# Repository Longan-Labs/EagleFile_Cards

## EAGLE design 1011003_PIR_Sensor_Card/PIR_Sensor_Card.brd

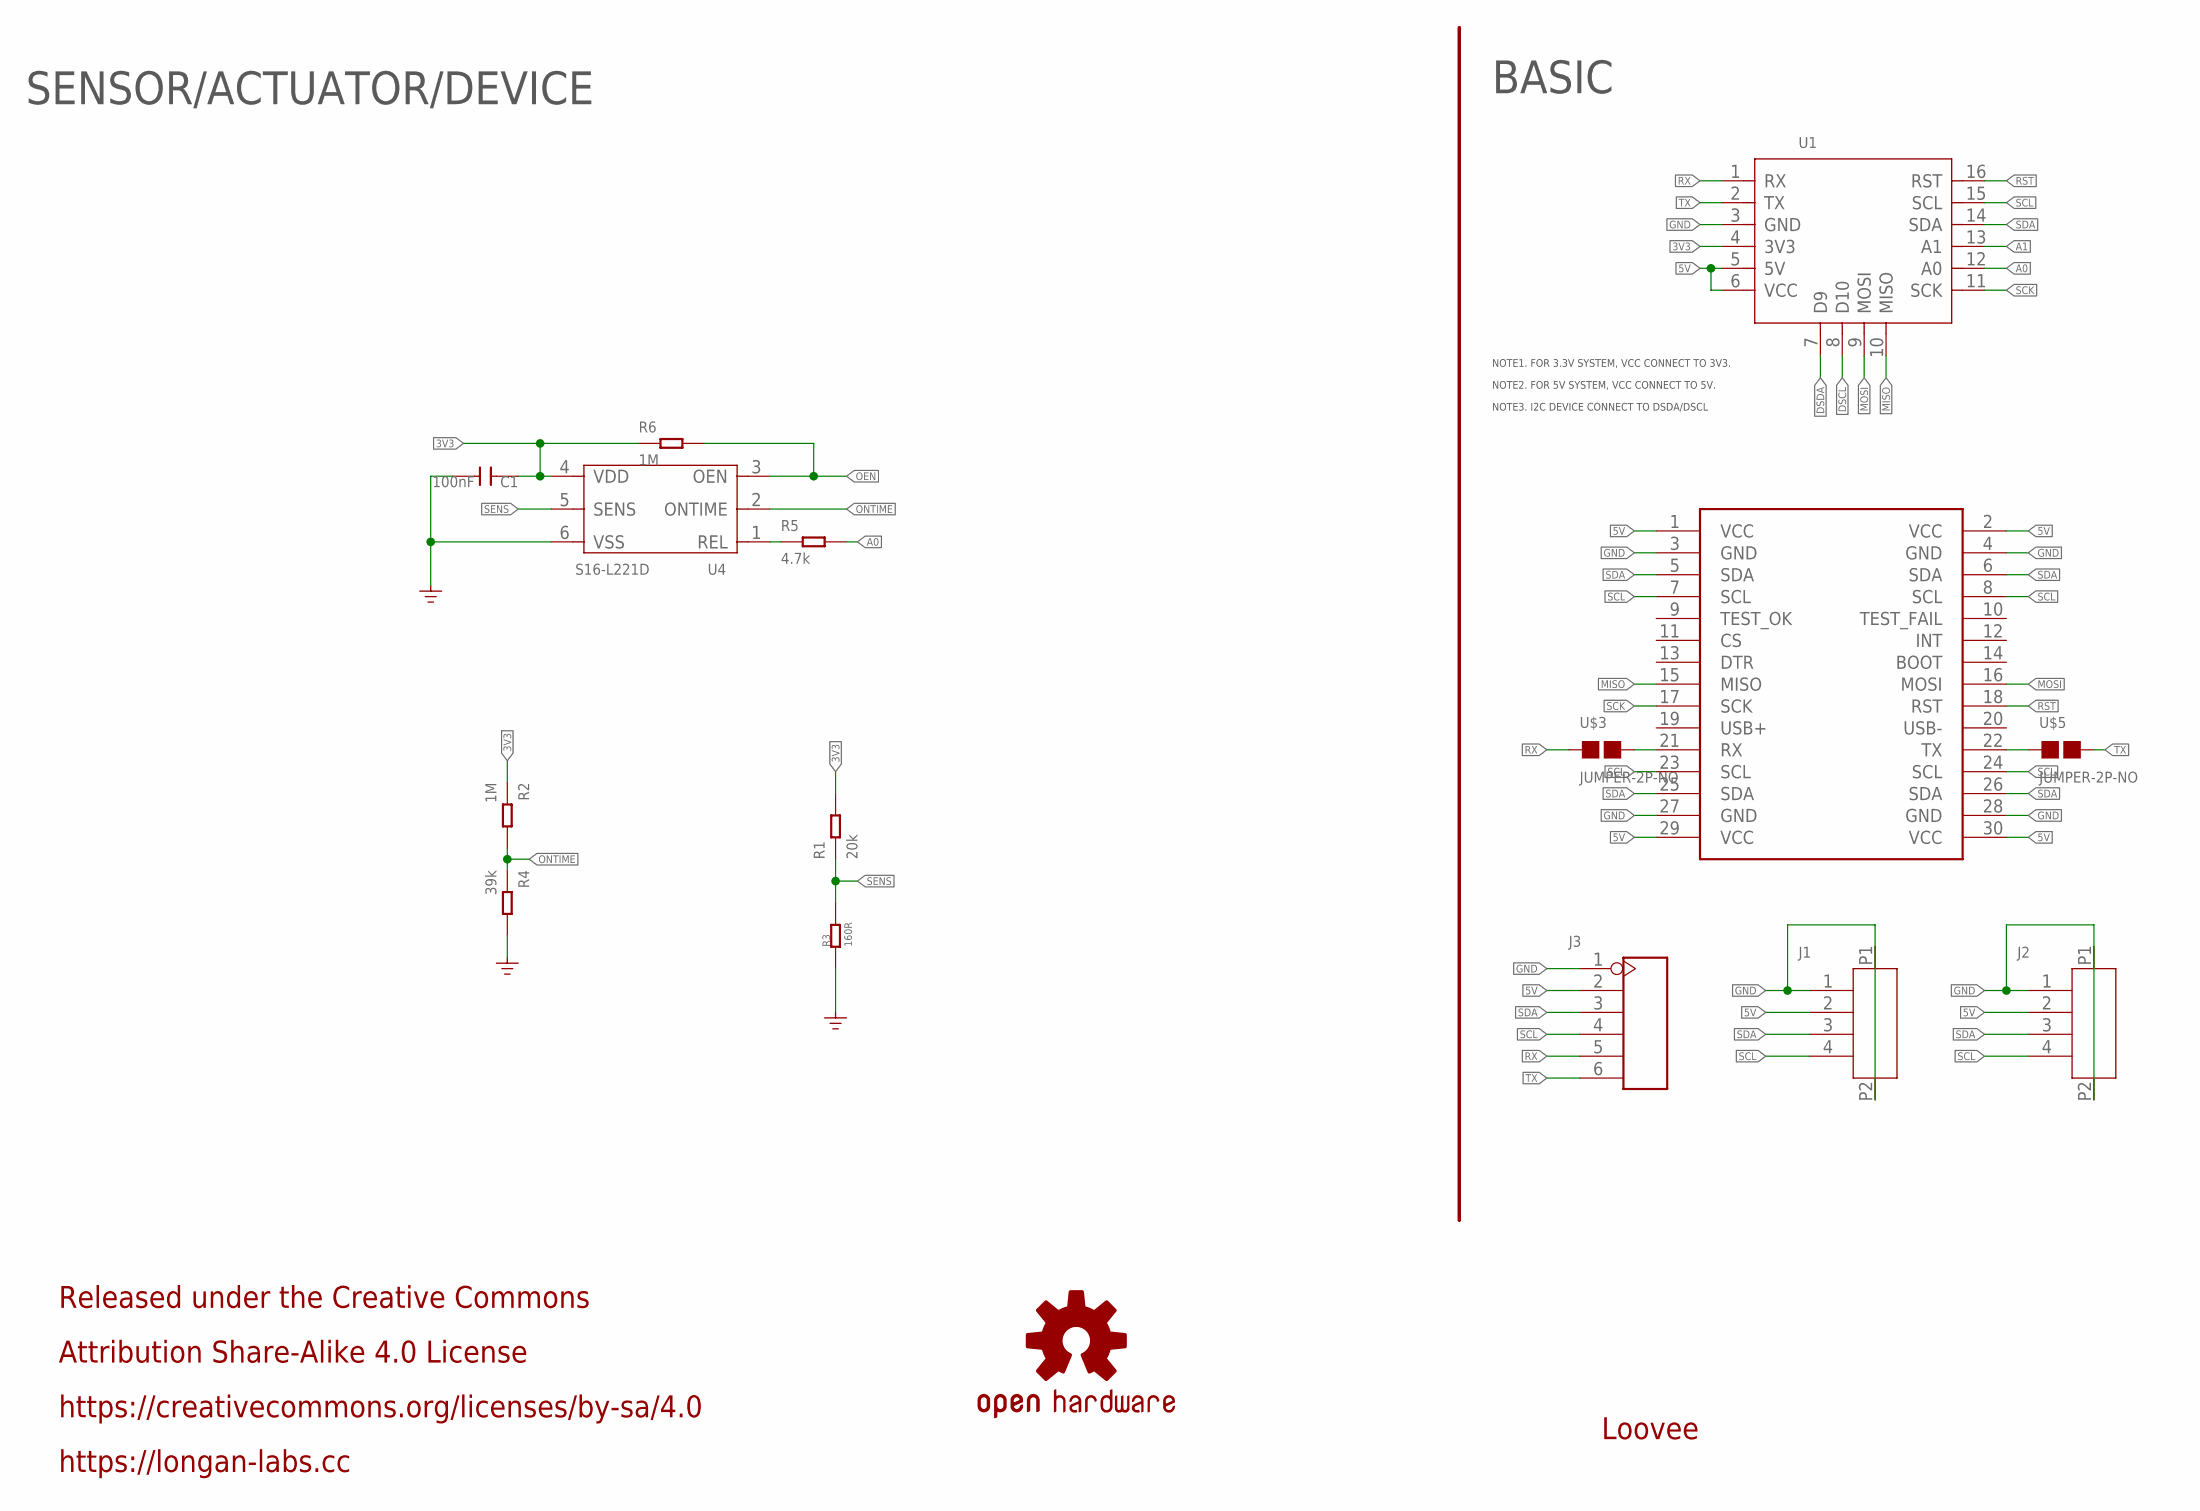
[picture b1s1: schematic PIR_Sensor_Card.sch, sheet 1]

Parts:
C1: 100nF; C0603
J1, J2: HEADER-4P-1.0; 4P-1.0-90D
J3: HEADER-6P-55/35MIL; H6-2.54
LOGO2: OSHW-LOGOS; OSHW-LOGO-S
MOUDLE1: MOUDLE-2X15P-2.54'BOARD'; MOUDLE-2X15P-2.54
R1: 20k; R0603
R2, R6: 1M; R0603
R3: 160R; R0603
R4: 39k; R0603
R5: 4.7k; R0603
U1: MOUDLE-CARDS; 16P-2.0-CARDS
U4: S16-L221D; 6P-SMD-6X6MM
U$3, U$5: JUMPER-2P-NO; 2P-SMD-NO

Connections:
3V3: C1.1, R1.2, R2.1, R6.1, U1.4 (3V3), U4.4 (VDD)
5V: J1.2, J2.2, J3.2, MOUDLE1.1 (VCC), MOUDLE1.2 (VCC), MOUDLE1.29 (VCC), MOUDLE1.30 (VCC), U1.5 (5V), U1.6 (VCC)
A0: R5.2, U1.12 (A0)
A1: U1.13 (A1)
DSCL: U1.8 (D10)
DSDA: U1.7 (D9)
GND: C1.2, J1.1, J1.P1, J1.P2, J2.1, J2.P1, J2.P2, J3.1, MOUDLE1.3 (GND), MOUDLE1.4 (GND), MOUDLE1.27 (GND), MOUDLE1.28 (GND), R3.1, R4.2, U1.3 (GND), U4.6 (VSS)
MISO: MOUDLE1.15 (MISO), U1.10 (MISO)
MOSI: MOUDLE1.16 (MOSI), U1.9 (MOSI)
unnamed: R5.1, U4.1 (REL)
unnamed: MOUDLE1.21 (RX), U$3.2
unnamed: MOUDLE1.22 (TX), U$5.1
OEN: R6.2, U4.3 (OEN)
ONTIME: R2.2, R4.1, U4.2 (ONTIME)
RST: MOUDLE1.18 (RST), U1.16 (RST)
RX: J3.5, U1.1 (RX), U$3.1
SCK: MOUDLE1.17 (SCK), U1.11 (SCK)
SCL: J1.4, J2.4, J3.4, MOUDLE1.7 (SCL), MOUDLE1.8 (SCL), MOUDLE1.23 (SCL), MOUDLE1.24 (SCL), U1.15 (SCL)
SDA: J1.3, J2.3, J3.3, MOUDLE1.5 (SDA), MOUDLE1.6 (SDA), MOUDLE1.25 (SDA), MOUDLE1.26 (SDA), U1.14 (SDA)
SENS: R1.1, R3.2, U4.5 (SENS)
TX: J3.6, U1.2 (TX), U$5.2

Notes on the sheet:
BASIC
Loovee
NOTE1. FOR 3.3V SYSTEM, VCC CONNECT TO 3V3.
NOTE2. FOR 5V SYSTEM, VCC CONNECT TO 5V.
NOTE3. I2C DEVICE CONNECT TO DSDA/DSCL
SENSOR/ACTUATOR/DEVICE
Released under the Creative Commons
Attribution Share-Alike 4.0 License
https://creativecommons.org/licenses/by-sa/4.0
https://longan-labs.cc

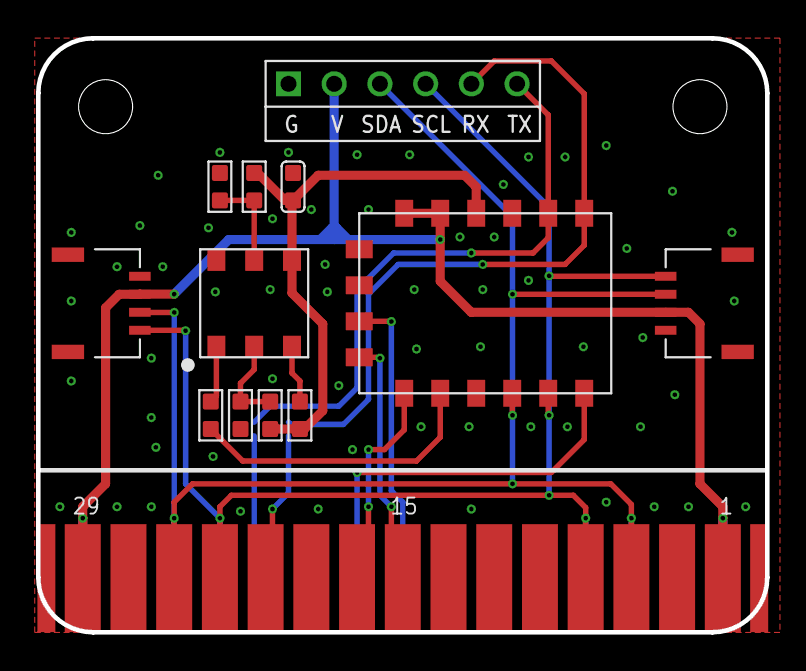
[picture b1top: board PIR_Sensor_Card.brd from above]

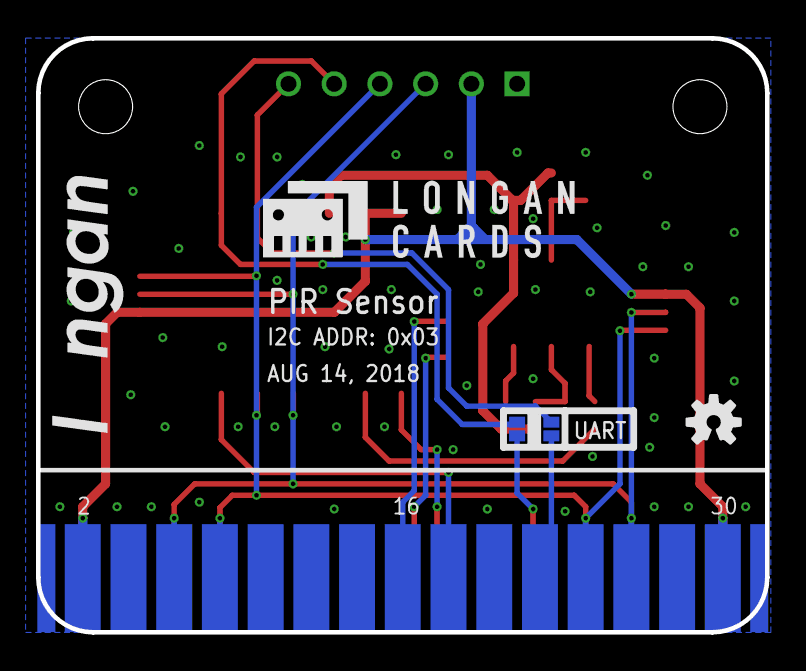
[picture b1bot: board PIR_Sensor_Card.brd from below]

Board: 2 copper layers, 40.5 x 33.0 mm, 18 parts (5 on the bottom side), 18 nets.

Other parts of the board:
U$1: LONGAN-CARDS-MIDDLE
U$7: LONGAN-COPPER-SMALLER

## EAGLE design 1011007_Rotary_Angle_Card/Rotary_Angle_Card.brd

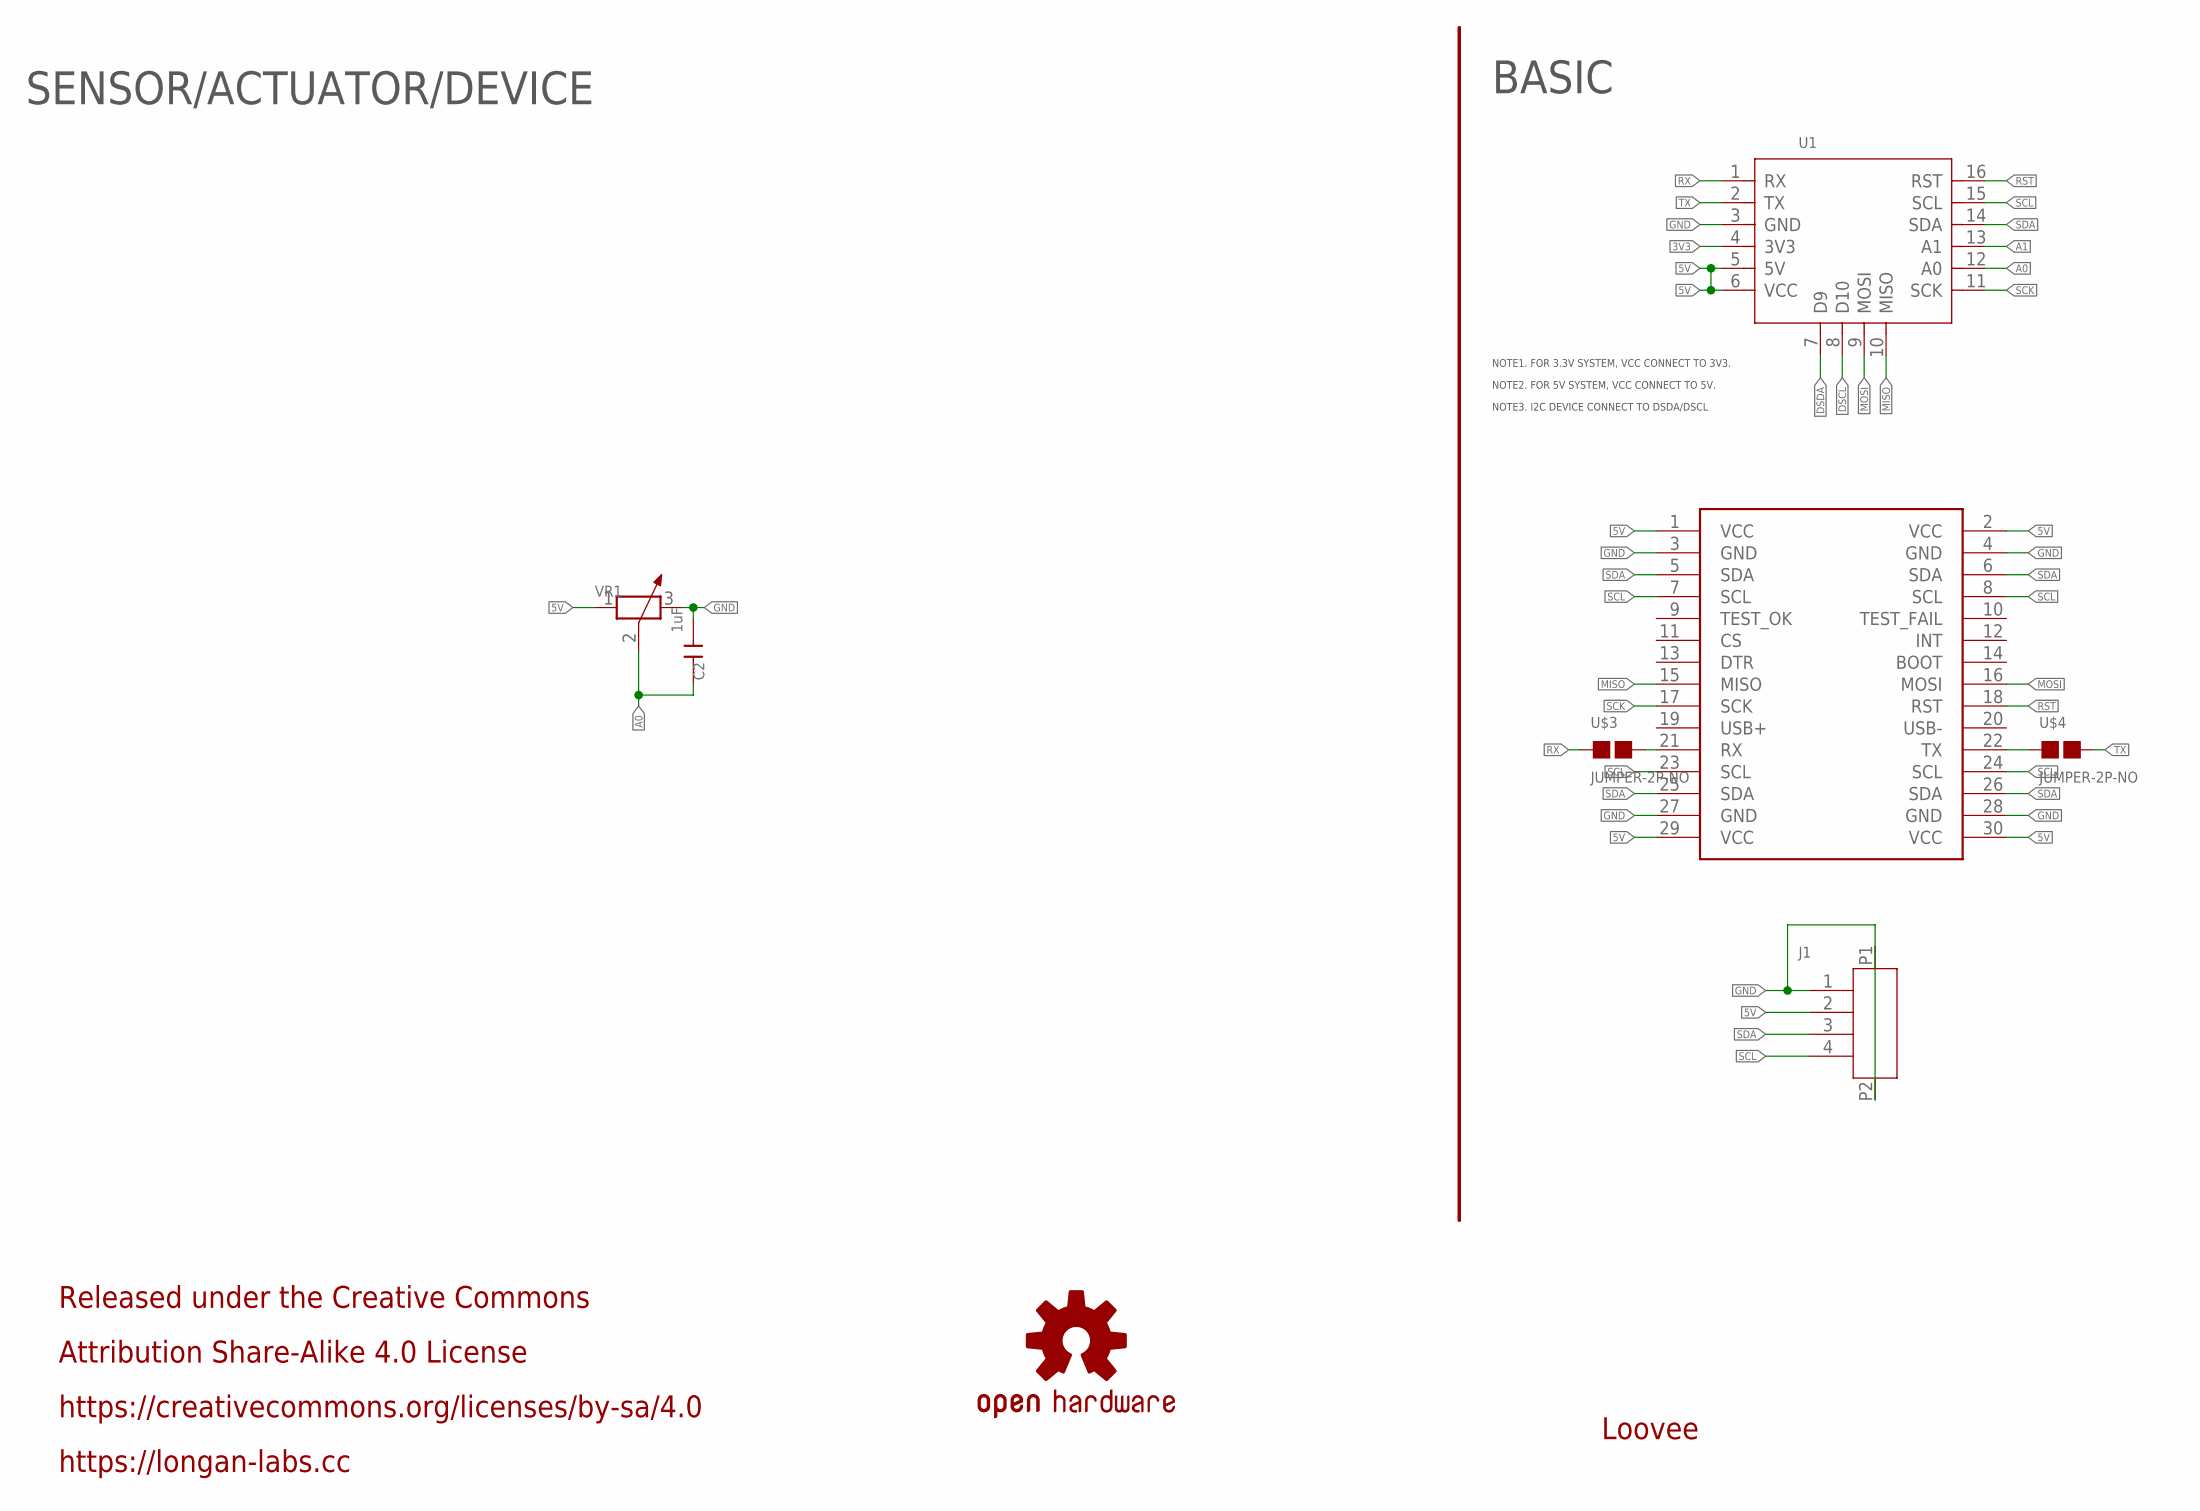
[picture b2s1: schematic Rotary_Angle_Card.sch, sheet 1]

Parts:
C2: 1uF; C0603
J1: HEADER-4P-1.0; 4P-1.0-90D
LOGO2: OSHW-LOGOS; OSHW-LOGO-S
MOUDLE1: MOUDLE-2X15P-2.54'BOARD'; MOUDLE-2X15P-2.54
U1: MOUDLE-CARDS; 16P-2.0-CARDS
U$3, U$4: JUMPER-2P-NO; 2P-SMD-NO
VR1: RES-ADJ; 2+3P-L11*W9.8*H12MM

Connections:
3V3: U1.4 (3V3)
5V: J1.2, MOUDLE1.1 (VCC), MOUDLE1.2 (VCC), MOUDLE1.29 (VCC), MOUDLE1.30 (VCC), U1.5 (5V), U1.6 (VCC), VR1.1
A0: C2.1, U1.12 (A0), VR1.2 (3)
A1: U1.13 (A1)
DSCL: U1.8 (D10)
DSDA: U1.7 (D9)
GND: C2.2, J1.1, J1.P1, J1.P2, MOUDLE1.3 (GND), MOUDLE1.4 (GND), MOUDLE1.27 (GND), MOUDLE1.28 (GND), U1.3 (GND), VR1.3 (2)
MISO: MOUDLE1.15 (MISO), U1.10 (MISO)
MOSI: MOUDLE1.16 (MOSI), U1.9 (MOSI)
unnamed: MOUDLE1.21 (RX), U$3.2
unnamed: MOUDLE1.22 (TX), U$4.1
RST: MOUDLE1.18 (RST), U1.16 (RST)
RX: U1.1 (RX), U$3.1
SCK: MOUDLE1.17 (SCK), U1.11 (SCK)
SCL: J1.4, MOUDLE1.7 (SCL), MOUDLE1.8 (SCL), MOUDLE1.23 (SCL), MOUDLE1.24 (SCL), U1.15 (SCL)
SDA: J1.3, MOUDLE1.5 (SDA), MOUDLE1.6 (SDA), MOUDLE1.25 (SDA), MOUDLE1.26 (SDA), U1.14 (SDA)
TX: U1.2 (TX), U$4.2

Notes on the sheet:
BASIC
Loovee
NOTE1. FOR 3.3V SYSTEM, VCC CONNECT TO 3V3.
NOTE2. FOR 5V SYSTEM, VCC CONNECT TO 5V.
NOTE3. I2C DEVICE CONNECT TO DSDA/DSCL
SENSOR/ACTUATOR/DEVICE
Released under the Creative Commons
Attribution Share-Alike 4.0 License
https://creativecommons.org/licenses/by-sa/4.0
https://longan-labs.cc

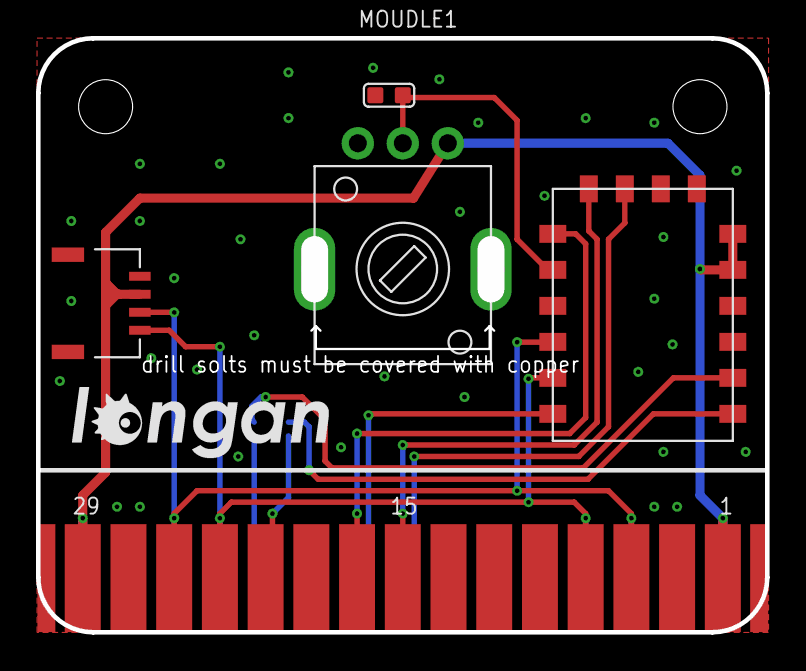
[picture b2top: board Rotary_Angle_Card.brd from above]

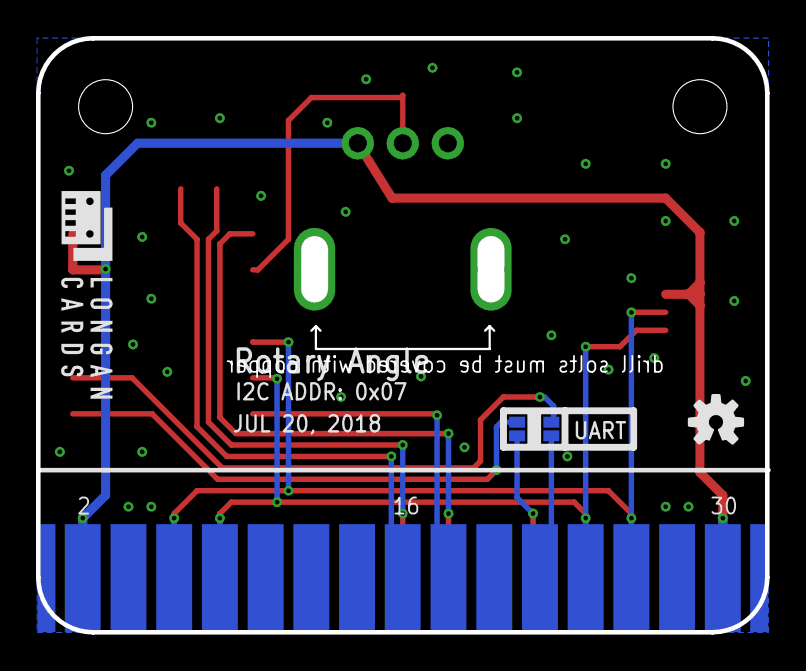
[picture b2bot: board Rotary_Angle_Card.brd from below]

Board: 2 copper layers, 40.5 x 33.0 mm, 10 parts (4 on the bottom side), 13 nets.

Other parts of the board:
U$1: LONGAN-CARDS-SMALL
U$2: LONGAN-SILK-SMALLER

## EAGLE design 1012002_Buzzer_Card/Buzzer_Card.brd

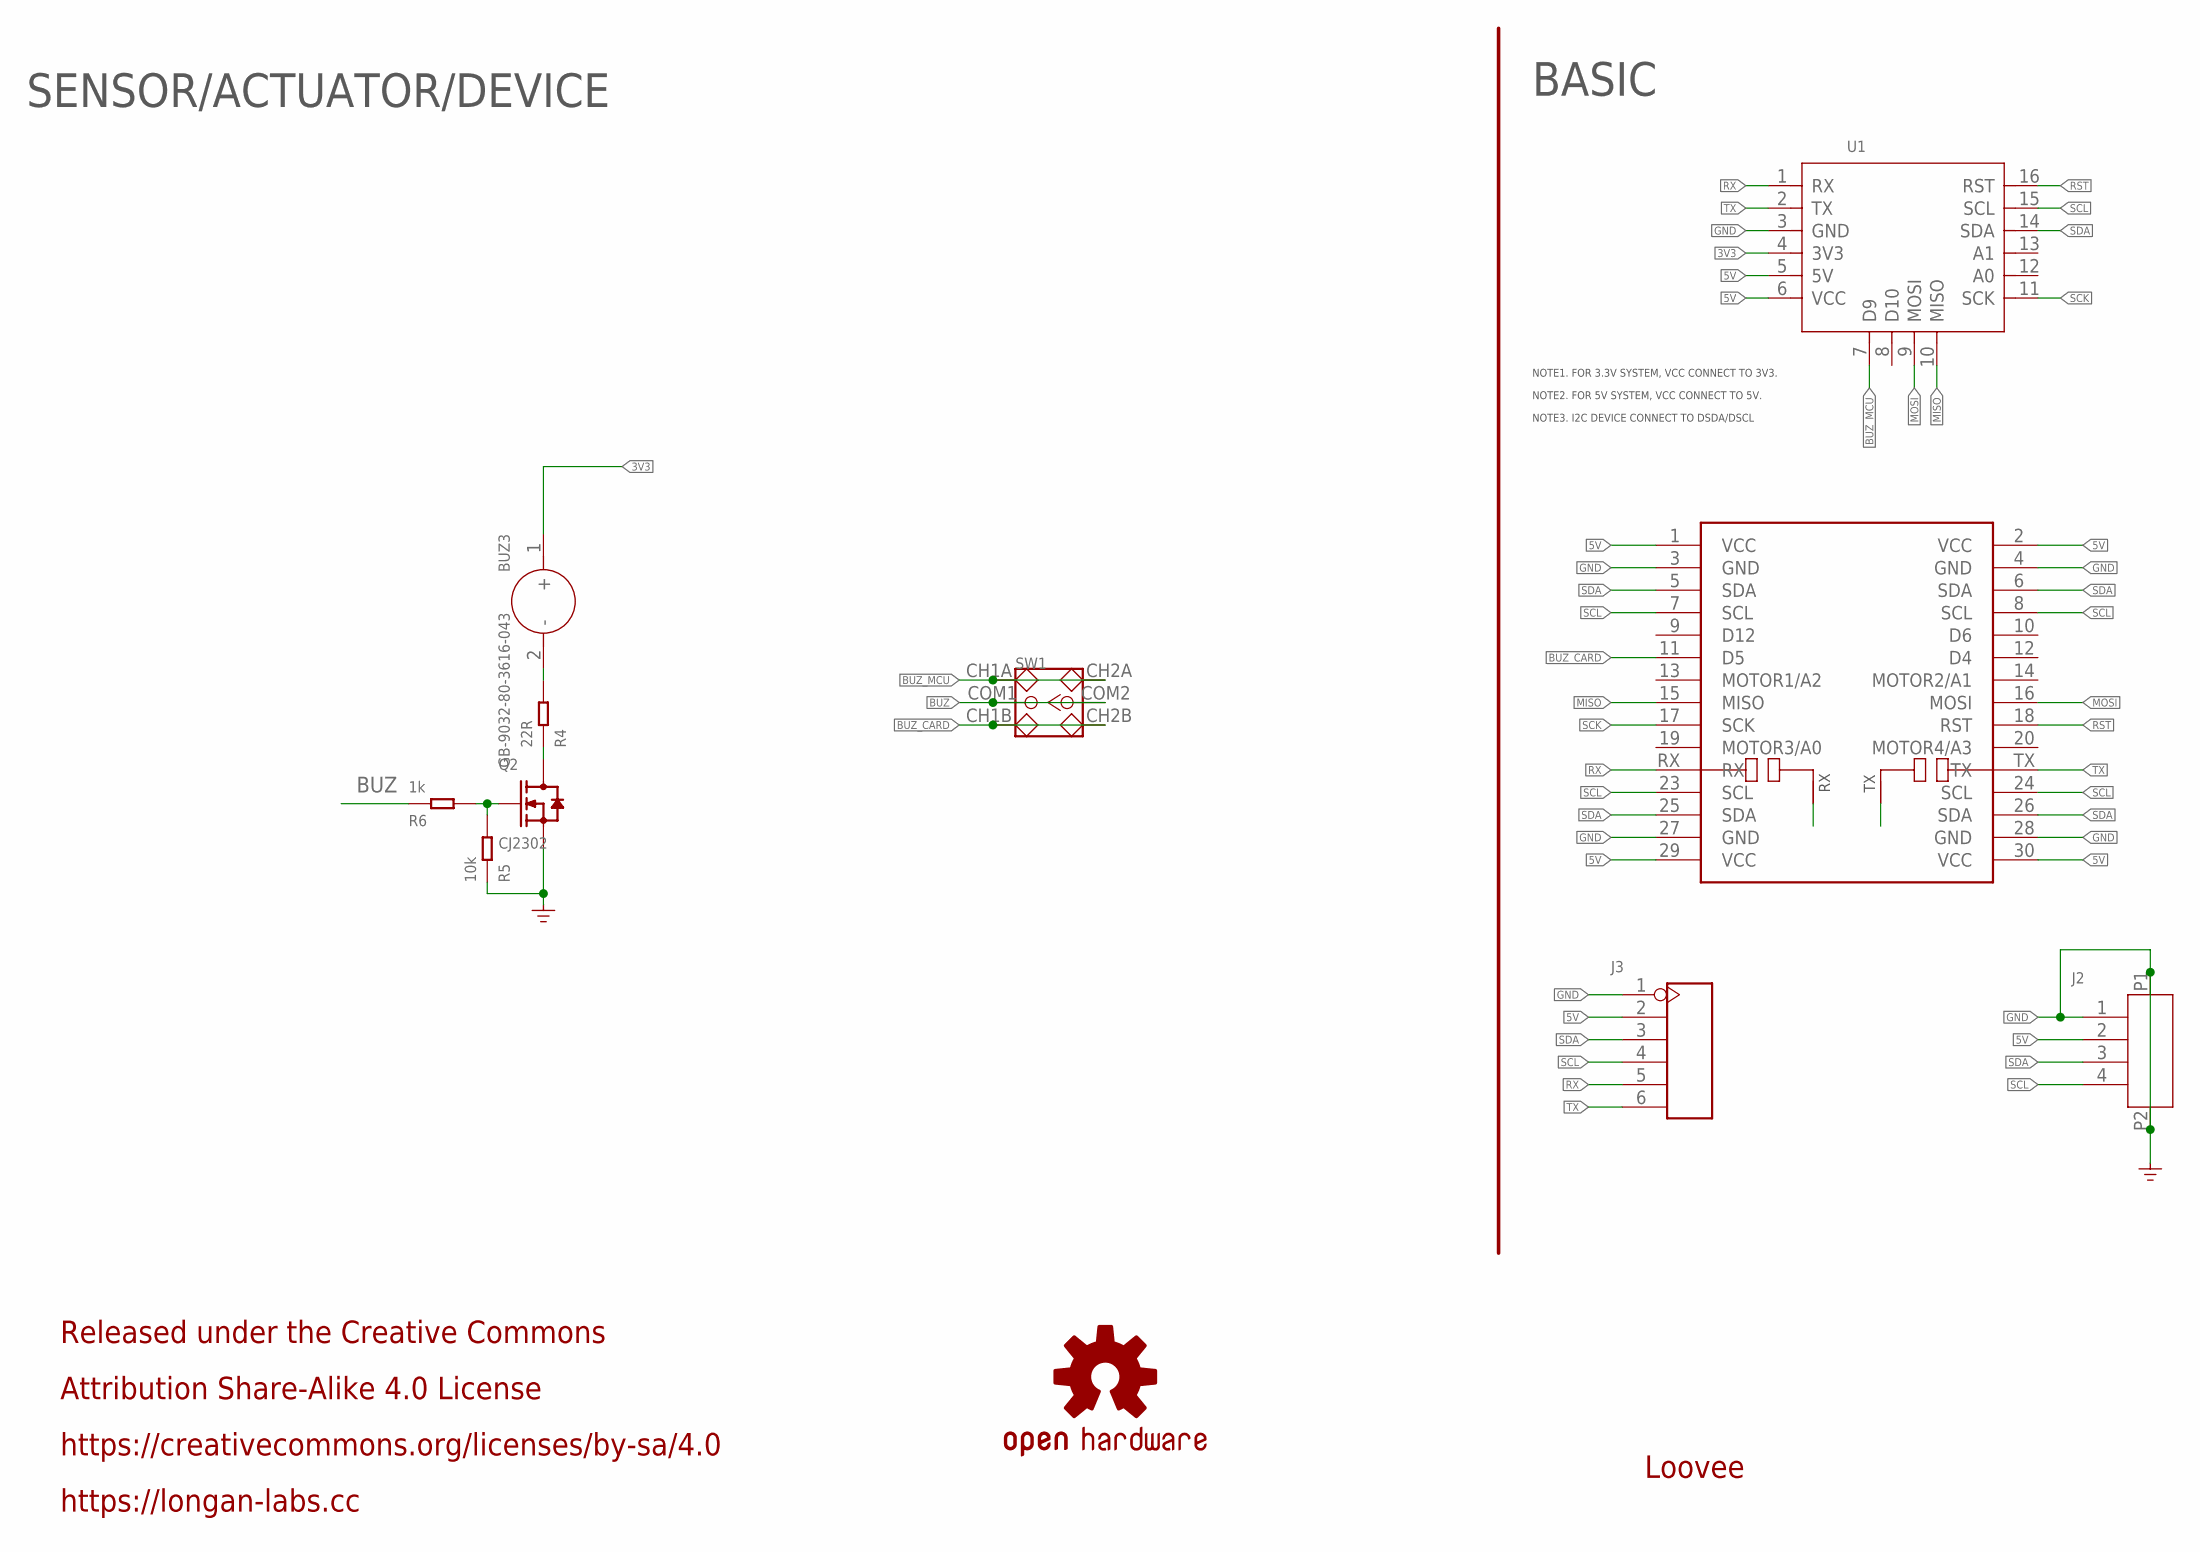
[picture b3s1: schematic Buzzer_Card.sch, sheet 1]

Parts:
BUZ3: GB-9032-80-3616-043; BZ2-SMD-9X10.6X3.2MM
J2: HEADER-4P-1.0; 4P-1.0-90D
J3: HEADER-6P-55/35MIL; H6-2.54
LOGO2: OSHW-LOGOS; OSHW-LOGO-S
MOUDLE2: MOUDLE-CARDS-UART'BOARD'; MOUDLE-2X15P-UART
Q2: CJ2302; SOT-23
R4: 22R; R0603
R5: 10k; R0603
R6: 1k; R0603
SW1: SWITCH-2CH-6P-SMD; SW6-2.54-SMD-7.0X3.5X1.5MM
U1: MOUDLE-CARDS; 16P-2.0-CARDS

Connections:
3V3: BUZ3.1 (+), U1.4 (3V3)
5V: J2.2, J3.2, MOUDLE2.1 (VCC), MOUDLE2.2 (VCC), MOUDLE2.29 (VCC), MOUDLE2.30 (VCC), U1.5 (5V), U1.6 (VCC)
BUZ: R6.1, SW1.COM1, SW1.COM2
BUZ_CARD: MOUDLE2.11 (D5), SW1.CH1B, SW1.CH2B
BUZ_MCU: SW1.CH1A, SW1.CH2A, U1.7 (D9)
GND: J2.1, J2.P1, J2.P2, J3.1, MOUDLE2.3 (GND), MOUDLE2.4 (GND), MOUDLE2.27 (GND), MOUDLE2.28 (GND), Q2.2 (S), R5.1, U1.3 (GND)
MISO: MOUDLE2.15 (MISO), U1.10 (MISO)
MOSI: MOUDLE2.16 (MOSI), U1.9 (MOSI)
unnamed: Q2.3 (D), R4.1
unnamed: MOUDLE2.RX/N1 (RX/N), MOUDLE2.RX/N2 (RX/N)
unnamed: Q2.1 (G), R5.2, R6.2
unnamed: BUZ3.2 (-), R4.2
unnamed: MOUDLE2.TX/N1 (TX/N), MOUDLE2.TX/N2 (TX/N)
RST: MOUDLE2.18 (RST), U1.16 (RST)
RX: J3.5, MOUDLE2.RX, U1.1 (RX)
SCK: MOUDLE2.17 (SCK), U1.11 (SCK)
SCL: J2.4, J3.4, MOUDLE2.7 (SCL), MOUDLE2.8 (SCL), MOUDLE2.23 (SCL), MOUDLE2.24 (SCL), U1.15 (SCL)
SDA: J2.3, J3.3, MOUDLE2.5 (SDA), MOUDLE2.6 (SDA), MOUDLE2.25 (SDA), MOUDLE2.26 (SDA), U1.14 (SDA)
TX: J3.6, MOUDLE2.TX, U1.2 (TX)

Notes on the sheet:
BASIC
Loovee
NOTE1. FOR 3.3V SYSTEM, VCC CONNECT TO 3V3.
NOTE2. FOR 5V SYSTEM, VCC CONNECT TO 5V.
NOTE3. I2C DEVICE CONNECT TO DSDA/DSCL
SENSOR/ACTUATOR/DEVICE
Released under the Creative Commons
Attribution Share-Alike 4.0 License
https://creativecommons.org/licenses/by-sa/4.0
https://longan-labs.cc

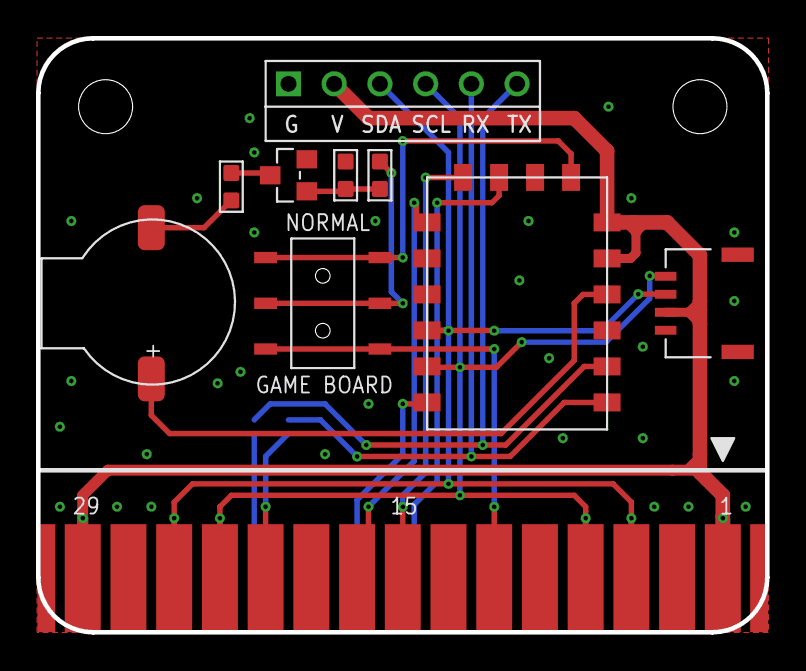
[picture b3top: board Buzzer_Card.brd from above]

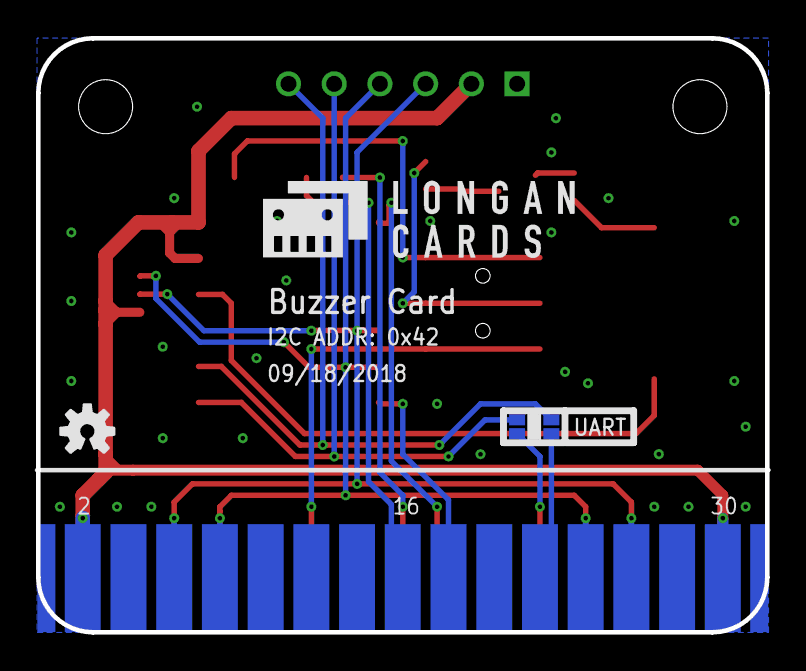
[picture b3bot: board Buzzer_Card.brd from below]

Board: 2 copper layers, 40.5 x 33.0 mm, 12 parts (2 on the bottom side), 19 nets.

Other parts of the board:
U$1: LONGAN-CARDS-MIDDLE

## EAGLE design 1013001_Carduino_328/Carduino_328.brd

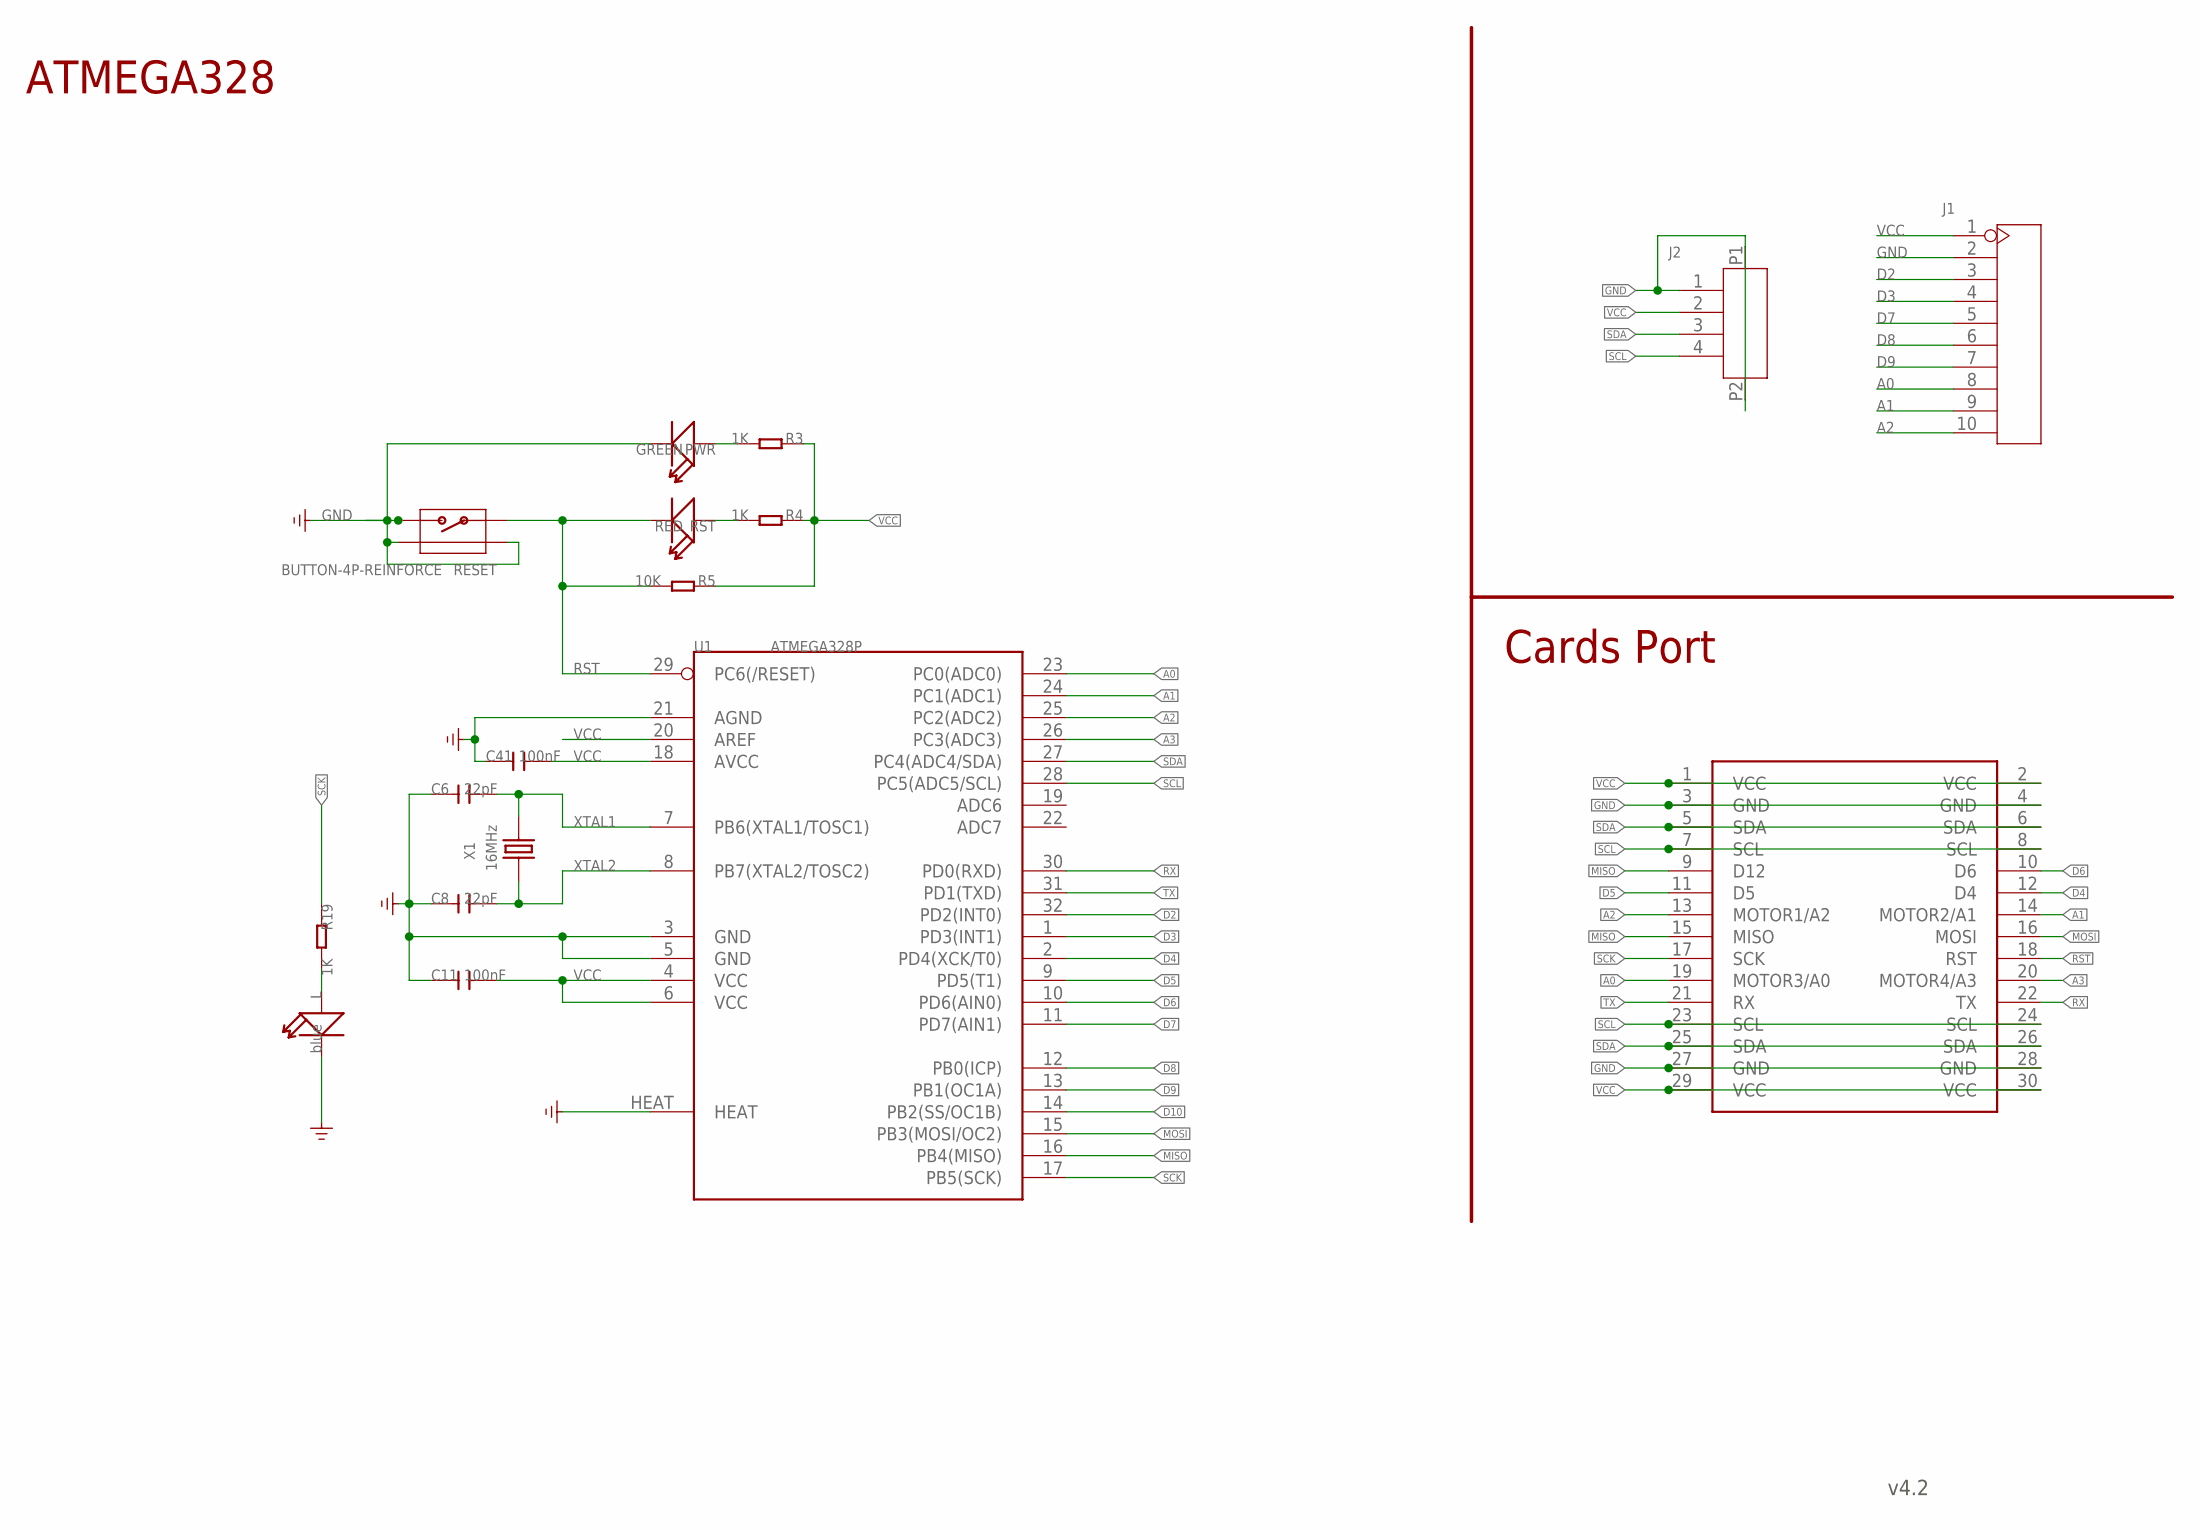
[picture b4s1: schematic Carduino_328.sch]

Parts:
C6, C8: 22pF; C0603
C11, C41: 100nF; C0603
J1: HEADER-10P-2.54; H10-2.54
J2: HEADER-4P-1.0; 4P-1.0-90D
L: blue; LED-0603
MOUDLE1: MOUDLE-2X15P-MCU'BOARD'; MOUDLE-2X15P-2.54
PWR: GREEN; LED-0603
R3, R4, R19: 1K; R0603
R5: 10K; R0603
RESET: BUTTON-4P-REINFORCE; 4P-SMD-7X3.5X3.5H
RST: RED; LED-0603
U1: ATMEGA328P; MLF32X
X1: 16MHz; 2P-SMD-5X3.2

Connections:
A0: J1.8, MOUDLE1.19 (MOTOR3/A0), U1.23 (PC0(ADC0))
A1: J1.9, MOUDLE1.14 (MOTOR2/A1), U1.24 (PC1(ADC1))
A2: J1.10, MOUDLE1.13 (MOTOR1/A2), U1.25 (PC2(ADC2))
A3: MOUDLE1.20 (MOTOR4/A3), U1.26 (PC3(ADC3))
D2: J1.3, U1.32 (PD2(INT0))
D3: J1.4, U1.1 (PD3(INT1))
D4: MOUDLE1.12 (D4), U1.2 (PD4(XCK/T0))
D5: MOUDLE1.11 (D5), U1.9 (PD5(T1))
D6: MOUDLE1.10 (D6), U1.10 (PD6(AIN0))
D7: J1.5, U1.11 (PD7(AIN1))
D8: J1.6, U1.12 (PB0(ICP))
D9: J1.7, U1.13 (PB1(OC1A))
D10: U1.14 (PB2(SS/OC1B))
GND: C6.1, C8.1, C11.1, C41.1, J1.2, J2.1, J2.P1, J2.P2, L.-, MOUDLE1.3 (GND), MOUDLE1.4 (GND), MOUDLE1.27 (GND), MOUDLE1.28 (GND), PWR.-, RESET.2, RESET.S1, RESET.S2, U1.3 (GND), U1.5 (GND), U1.21 (AGND), U1.HEAT
MISO: MOUDLE1.9 (D12), MOUDLE1.15 (MISO), U1.16 (PB4(MISO))
MOSI: MOUDLE1.16 (MOSI), U1.15 (PB3(MOSI/OC2))
unnamed: L.+, R19.2
unnamed: PWR.+, R3.2
unnamed: R4.2, RST.+
RST: MOUDLE1.18 (RST), R5.2, RESET.1, RST.-, U1.29 (PC6(/RESET))
RX: MOUDLE1.22 (TX), U1.30 (PD0(RXD))
SCK: MOUDLE1.17 (SCK), R19.1, U1.17 (PB5(SCK))
SCL: J2.4, MOUDLE1.7 (SCL), MOUDLE1.8 (SCL), MOUDLE1.23 (SCL), MOUDLE1.24 (SCL), U1.28 (PC5(ADC5/SCL))
SDA: J2.3, MOUDLE1.5 (SDA), MOUDLE1.6 (SDA), MOUDLE1.25 (SDA), MOUDLE1.26 (SDA), U1.27 (PC4(ADC4/SDA))
TX: MOUDLE1.21 (RX), U1.31 (PD1(TXD))
VCC: C11.2, C41.2, J1.1, J2.2, MOUDLE1.1 (VCC), MOUDLE1.2 (VCC), MOUDLE1.29 (VCC), MOUDLE1.30 (VCC), R3.1, R4.1, R5.1, U1.4 (VCC), U1.6 (VCC), U1.18 (AVCC), U1.20 (AREF)
XTAL1: C6.2, U1.7 (PB6(XTAL1/TOSC1)), X1.2
XTAL2: C8.2, U1.8 (PB7(XTAL2/TOSC2)), X1.1

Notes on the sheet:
v4.2
ATMEGA328
Cards Port

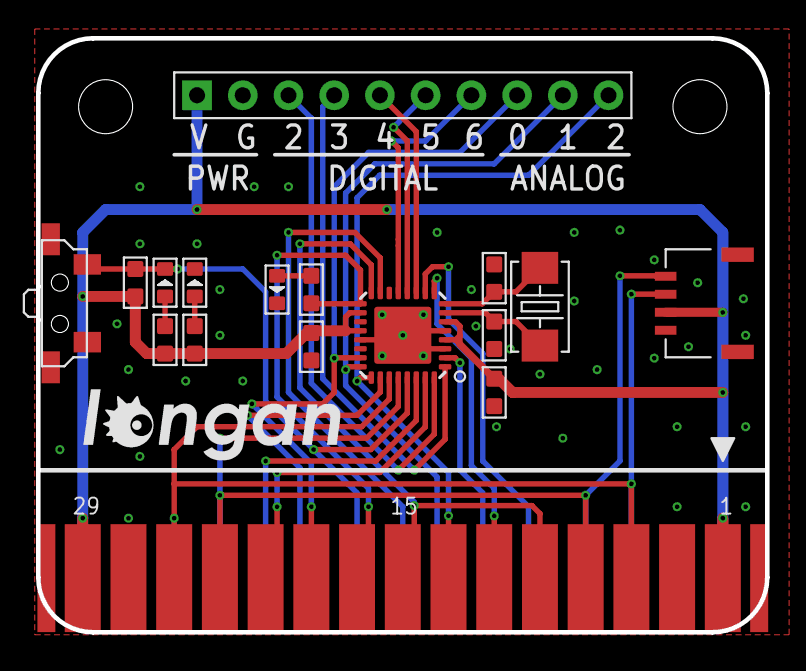
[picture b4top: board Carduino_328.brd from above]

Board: 2 copper layers, 40.5 x 33.0 mm, 19 parts (1 on the bottom side), 27 nets.

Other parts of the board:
U$1: LONGAN-CARDS-MIDDLE
U$3: LONGAN-SILK-SMALLER

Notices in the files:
parts and their libraries:
SparkFun-Aesthetics: Licensing: CC v3.0 Share-Alike You are welcome to use this library for commercial purposes.
